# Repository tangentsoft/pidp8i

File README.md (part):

# Getting Started with the PiDP-8/I Software

## Orientation

You will be reading this either:

*   …[online][tlrm], within [the Fossil project repository][home]; or
*   …as a text file within the [source packages][src]; or
*   …in the read-only [GitHub mirror][ghm].

The latter two are secondary outputs from the first, being the PiDP-8/I
software development project’s home.

This is open source software: you are welcome to
[contribute to the project][ctrb].

[ctrb]: https://tangentsoft.com/pidp8i/doc/trunk/CONTRIBUTING.md
[ghm]:  https://github.com/tangentsoft/pidp8i
[home]: https://tangentsoft.com/pidp8i/
[src]:  https://tangentsoft.com/pidp8i/#src
[tlrm]: https://tangentsoft.com/pidp8i/doc/trunk/README.md

## Prerequisites

*   A Raspberry Pi with the 40-pin GPIO connector.

*   An SD card imaged with Raspberry Pi OS, either [stock][rpios] or
    [modified by us][bosi].

*   This software distribution, unpacked somewhere convenient within the
    filesystem on the Raspberry Pi. That’s already done on [our modified
    OS images][bosi], in `~/pidp8i`. When adding it to the stock OS, we
    recommend that you unpack it in your `HOME` directory or somewhere
    else your user has read/write access.

*   While those with no Linux and Raspberry Pi knowledge may be able to
    follow our instructions blindly, we recommend that such persons look
    at [the official Raspberry Pi documentation][rpfd], particularly
    their [Linux][rpfl] and [Raspberry Pi OS][rpfr] guides. The book
    "[Linux for Makers][lfm]" by Aaron Newcomb is also well-reviewed.

*   Building the software requires several tools and libraries, some of
    which you may not already have.

    On Raspberry Pi OS, say:

        $ sudo apt update
        $ sudo apt install build-essential libraspberrypi-dev \
             libncurses-dev perl python3-pexpect python3-yaml

    Under Homebrew, such as on macOS, say instead:

        $ brew install make perl python
        $ pip3 install --user pexpect pyyaml

    On [other compatible OSes][othos], you may need different commands.

[bosi]:  https://tangentsoft.com/pidp8i/#bosi
[lfm]:   https://www.makershed.com/products/make-linux-for-makers
[othos]: https://tangentsoft.com/pidp8i/wiki?name=OS+Compatibility
[rpfd]:  https://www.raspberrypi.org/documentation/
[rpfl]:  https://www.raspberrypi.org/documentation/linux/
[rpfr]:  https://www.raspberrypi.com/documentation/computers/os.html
[rpios]: https://www.raspberrypi.org/software/

## Enabling the SSH Server 

[That topic is covered elsewhere](./doc/OS-images.md#sshd).

## Preparing Your Pi 

If you’ve just barely unpacked Raspberry Pi OS onto an SD card and are
now trying to get the PiDP-8/I software distribution working on it, stop
and go through the [Rasbperry Pi documentation][rpd] first. At the
absolute minimum, run `raspi-config` and make sure the Localization
settings are correct. The defaults are for the United Kingdom, home of
the Raspberry Pi Foundation, so unless you live there, the defaults are
probably incorrect for *your* location.

[rpd]: https://www.raspberrypi.org/documentation/

## Getting the Software onto Your Pi 

This section is for those reading this on [our project home site][home]
or via [its GitHub mirror][ghm]. If you are instead reading this as the
`README.md` file within an unpacked distribution of the PiDP-8/I
software, [skip to the next section](#configuring).

### Transferring the Source Tarball to the Pi 

There are many ways to get the `*.tar.gz` file onto your Pi:

1.  **Copy the file to the SD card** you're using to boot the Pi.
    When inserted into a Mac or Windows PC, typically only the `/boot`
    partition mounts as a drive your OS can see.  (There's a much
    larger partition on the SD card, but most PCs cannot see it.)
    There should be enough free space left in this small partition to
    copy the tarball over.  When you boot the Pi up with that SD card,
    you will find it in `/boot`.

2.  **Pull the file down to the Pi** over the web, directly to the Pi:

        $ wget -O pidp8i.tar.gz https://goo.gl/JowPoC

    That will get you a file called `pidp8i.tar.gz` in the current
    working directory containing the latest *stable release.* To get the
    bleeding edge tip-of-trunk version instead, say:

        $ wget -O pidp8i.tar.gz https://tangentsoft.com/pidp8i/tarball

3.  **SCP the file over** to a running Pi from another machine.
    If your Pi has [OpenSSH installed and running](#sshd), you can use
    [WinSCP][wscp], [Cyberduck][cd], [FileZilla][fz] or another SCP
    or SFTP-compatible file transfer program to copy the file to the
    Pi over the network.

[cd]:   https://cyberduck.io/
[fz]:   https://filezilla-project.org/
[wscp]: https://winscp.net/eng/

4.  **Clone the Fossil repository** using the instructions in the
    [`CONTRIBUTING.md` file][ctrb]. (Best for experts or those who wish to
    become experts.)

Alternatively, switch to [the binary OS installation images][bosi],
which are a copy of Raspberry Pi OS as of our latest stable release,
with the PiDP-8/I software already downloaded, configured, and installed
for you.

### Unpacking the Software on Your Pi 

Having transferred the distribution file onto your Pi, unpack it with:

    $ tar xf pidp8i.tar.gz

## Configuring, Building and Installing 

For a stock build, say:

    $ cd ~/pidp8i
    $ ./configure && tools/mmake && sudo make install

You may want to add options to the `configure` step, described
[below](#options).

Subsequent software updates and rebuilds should not require that you
re-run the `configure` step manually, but if automatic re-configuration
fails, you can force it:

    $ make reconfig

The “`mmake`” step above will take quite a while to run, especially on
the slower Pi boards. The longest single step is building the OS/8 disk
packs from source media. Be patient; the build process almost certainly
isn’t frozen.

Only the `make install` step needs to be done via “`sudo`”. No other
step requires root privileges.

After running “`sudo make install`” the first time, you will have to log
out and back in to get the installation’s “bin” directory into your
`PATH`.

## Using the Software 

For the most part, this software distribution works like the [old stable
2015.12.15 distribution][osd]. Its [documentation][oprj] therefore
describes this software too, though there are [significant
differences][mdif].

Quick start:

1.  To start the simulator running in the background:

        $ pidp8i start

    This will happen automatically on reboot unless you disable the
    service, such as in order to run one of the various [forks of Deeper
    Thought][dt2].

2.  To attach your terminal to the running simulator, run the same
    script without an argument:

        $ pidp8i

3.  To detach from the simulator's terminal interface while leaving the
    PiDP-8/I simulator running, type <kbd>Ctrl-A d</kbd>.  You can
    re-attach to it later with a `pidp8i` command.

4.  To shut the simulator down while attached to its terminal interface,
    type <kbd>Ctrl-E</kbd> to pause the simulator, then at the `simh>`
    prompt type `quit`.  Type `help` at that prompt to get some idea of
    what else you can do with the simulator command language, or read
    the [SIMH Users' Guide][sdoc].

5.  To shut the simulator down from the command line:

        $ pidp8i stop

    That then lets you run something like [Incandescent Thought][ith]
    without conflict.

You might also find our [Learning More](/#learning) links helpful.

[ith]:     https://tangentsoft.com/pidp8i/wiki?name=Incandescent+Thought

## The Background Simulator Service 

The PiDP-8/I software distribution uses [systemd] to run the background
PDP-8 simulator as user-level service, so you needn’t give `sudo` on any
command to interact with that service, as you did in older versions of
the software.

Although you can give verbose `systemctl` commands like this:

    $ systemctl --user start pidp8i

…we’ve provided a wrapper for such commands:

    $ pidp8i start
    $ pidp8i stop
    $ pidp8i restart
    $ pidp8i status -l

*All* arguments are passed to `systemctl`, not just the first, so you
can pass any flags that `systemctl` accepts, as in the last example.

[systemd]: https://www.freedesktop.org/wiki/Software/systemd/

## Configure Script Options 

You can change many things about the way the software is built and
installed by giving options to the `configure` script:

### --prefix 

Perhaps the most widely useful `configure` script option is `--prefix`,
which lets you override the default installation directory, `/opt/pidp8i`.
There are many good reasons to change where the software gets installed,
but the default is also a good one, so unless you know for a fact that
you want to change this default, leave it alone.

For example, you might prefer that the installer put the built software
under your home directory.  This will do that:

    $ ./configure --prefix=$HOME/pidp8i && sudo make install

You might think that installing to a directory your user has complete
control over would remove the need for installing via `sudo`, but that
is not the case, since the installation script needs root privileges to
mark a few of the executables as having permission to run at high priority
levels, which improves the quality of the display, particularly with the
[incandescent lamp simulator][ils] feature enabled.

### --lowercase 

The American Standards Association (predecessor to ANSI) delivered the
second major version of the ASCII character encoding standard the same
year the first PDP-8 came out, 1965. The big new addition? Lowercase.

That bit of history means that when the PDP-8 was new, lowercase was a
fancy new feature in the computing industry. That, plus the memory
savings you get from storing [stripped ASCII][sa] as two 6-bit
characters per 12-bit PDP-8 word means that most PDP-8 software did not
expect to receive lowercase ASCII text, particularly the older software.

The PDP-8 lived long enough to see lowercase ASCII input become common
in the computing industry.

As a result, PDP-8 software reacts in many strange and wonderful
ways when you give it lowercase input. Some software copes nicely,
other software crashes, and some software just sits there dumbly
waiting for you to type something!

This configuration option lets you control how you want your simulated
PDP-8/I to react to lowercase input:

*   **auto** — The default is for the software to attempt to "do the
    right thing." The simulator is configured to send lowercase input to
    the PDP-8 software running on it. Where we have the skill, will,
    need, and time for it, we have [patched][tty] some of the software
    we distribute that otherwise would not do the right thing with
    lowercase input to make it do so.

    This is *not* the option you want if you are a purist.

*   **pass** — This passes keyboard input through to the simulator
    unchanged, and no patches are applied to the PDP-8 software we
    distribute.

    This is the option for historical purists. If you run into trouble
    getting the software to work as you expect when built in this mode,
    try enabling CAPS LOCK.

*   **upper** — This option tells the PDP-8 simulator to turn lowercase
    input into upper case. This is the behavior we used for all versions
    of the PiDP-8/I software up through v2017.04.04.  Essentially, it
    tells the software that you want it to behave as through you've got
    it connected to an uppercase-only terminal like the Teletype Model 33 ASR.

    The advantage of this mode is that you will have no problems running
    PDP-8 software that does not understand lowercase ASCII text.

    The disadvantage is obvious: you won't be able to input lowercase
    ASCII text.

    The SIMH option we enable in this mode is bidirectional, so that if
    you run a program that does emit lowercase ASCII text — such as Rick
    Murphy's version of Adventure — it will be uppercased, just like an
    ASR-33 would do.

    Another trap here is that the C programming language requires
    lowercase text, so you will get a warning if you leave the default
    option **--enable-os8-cc8** set. Pass **--disable-os8-cc8** when
    enabling **upper** mode.

[sa]:  http://homepage.cs.uiowa.edu/~jones/pdp8/faqs/#charsets
[tty]: https://tangentsoft.com/pidp8i/wiki?name=OS/8+Console+TTY+Setup

### --no-lamp-simulator 

If you build the software on a multi-core host, the PDP-8/I simulator is
normally built with the [incandescent lamp simulator][ils] feature,
which drives the LEDs in a way that mimics the incandescent lamps used
in the original PDP-8/I. (We call this the ILS for short.) This feature
takes too much CPU power to run on anything but a multi-core
Raspberry Pi, being the Pi 2 and newer full-sized boards, excluding
the Zero series.

If you configure the software on a single-core Pi — models A+, B+, and
Zero — the simulator uses the original low-CPU-usage LED driving method
instead. (a.k.a. NLS for short, named after this configuration option.)

Those on a multi-core host who want this low-CPU-usage LED driving
method can give the `--no-lamp-simulator` option to `configure`.  This
method not only uses less CPU, which may be helpful if you're trying to
run a lot of background tasks on your Pi 2 or Pi 3, it can also be
helpful when the CPU is [heavily throttled][thro].

### --serial-mod 

If you have done [Oscar's serial mod][sm1] to your PiDP-8/I PCB and the
Raspberry Pi you have connected to it, add `--serial-mod` to the
`configure` command above.

If you do not give this flag at `configure` time with these hardware
modifications in place, the front panel will not work correctly, and
trying to run the software may even crash the Pi.

If you give this flag and your PCBs are *not* modified, most of the
hardware will work correctly, but several lights and switches will not
work correctly.

### --alt-serial-mod 

This flag is for an [alternative serial mod by James L-W][sm2]. It
doesn't require mods to the Pi, and the mods to the PiDP-8/I board are
different from Oscar's.  This flag changes the GPIO code to work with
these modifications to the PiDP-8/I circuit design.

See the linked mailing list thread for details.

As with `--serial-mod`, you should only enable this flag if you have
actually done the mods as specified by James L-W.

This option is a pure alternative to [`--serial-mod`](#serial-mod): you
can leave both off, but you cannot pass both.

### --throttle <a id="throttle"</a>

See [`README-throttle.md`][thro] for the values this option takes.  If
you don't give this option, the simulator runs as fast as possible.

### --enable-savestate 

By default, the PiDP-8/I starts up with the core state undefined and
runs the boot script you’ve selected either with the IF switches or by
passing it on the command line to `pidp8i-sim` or `pdp8`.  This brings
the simulator up in a known state, with no persistence between restarts
other than what was written to the simulated storage devices before the
last shutdown.

On a real PDP-8 with core memory, however, the values in memory will
persist for weeks without power; core memory on a PDP-8 is not zeroed on
power-up, unlike RAM on a modern computer.  Since the CPU doesn’t start
executing anything on power-up in a stock PDP-8 configuration, this
means the user can toggle in a program/OS restart address with the
switch register (SR), load it into the program counter (PC) with the
Load Addr switch, then START the CPU to restart their program without
having to reload it from tape or disk.

There were also several power fail and restart options designed and made
available for the PDP-8 series throughout its lifetime. One of these —
the KP8-I for the PDP-8/I — would detect a power fail condition, then in
the brief time window while the power supply’s reservoir capacitors kept
the computer running, this option card would raise an interrupt, giving
a user-written routine up to 1 millisecond to save important registers
to core so they would persist through the power outage. Then on
power-up, it would start executing at core location 00000, where another
user routine would load those registers back from core to restart the
system where it left off before the power failed.

Giving this option gives roughtly the same effect for all generated boot
scripts: any time the simulator is shut down gracefully, it saves all
key simulator state — registers, core, device assignments, etc. — to a
disk file. Then on restart, that script will reload that saved state if
it finds the saved state file.

This is not identical to a KP8-I in that it doesn’t require any
user-written PDP-8 code to run, which is why it’s optional: it’s
ahistoric with respect to the way the included OSes normally ran.

In absence of a hardware option like the KP8-I, a more accurate
simulation would only save the core memory state to a host-side disk
file and reload it on simulator re-start. You can get that behavior atop
the current mechanism by adding commands like the following to each
bootscript you want to affect:

    EVAL HLT
    DEP L 0
    DEP AC 0
    DEP DF 0
    DEP IF 0
    DEP MQ 0
    DEP PC 0

That zeroes the key registers and prevents the CPU from running as it
normally would after giving the `RESTORE` command to SIMH.

### --disable-usb-automount 

When you install the software on a [systemd]-based Linux
system, we normally configure the OS to automatically mount USB drives
when they are initially plugged in, which allows the `SING_STEP` + `DF`
media image auto-attach feature to work smoothly. That is, if you plug
in a USB memory stick holding a `*.pt` file containing a paper tape
image, you want the simulator to be able to find it if you have the DF
switches set to 1, telling the PiDP-8/I front panel code to look for
something to attach to the simulator's paper tape reader.

This feature may interfere with other uses of USB, such as when booting
your Pi from an external USB hard disk drive. Give this option to
disable the feature.

(Alternately, you could modify our `etc/udev.rules` and/or
`bin/usb-mount` scripts so that they work cooperatively with your local
USB setup rather than conflicting with it.)

### --disable-cc8-cross 

Give this option if you do not want to build Ian Schofield's `cc8` C
cross-compiler on the host.

Because the cross-compiler is needed to build the CC8 native OS/8
compiler, disabling the cross-compiler also causes the native compiler
to be left off the bootable OS/8 RK05 disk image, as if you’d passed the
`--disable-os8-cc8` configuration option.

### --use-ock 

By default, the boot media used for the IF=0 and IF=7 cases is an
extended version of OS/8 V3D, as distributed by DEC, plus some patches
and third-party software additions, per the following sections.

For the late 2020 release, we have another more ambituous option, being
[the OS/8 Combined Kit][ock], which is the last complete release of OS/8
released by DEC. (See that link for details.)

Pass this option to boot OCK rather than OS/8 V3D.

[ock]: https://tangentsoft.com/pidp8i/dir?ci=tip&name=src/os8/ock

### --disable-os8-\* 

Several default components of the [OS/8 RK05 disk image](#os8di) used by
boot options IF=0 and IF=7 can be left out to save space and build time:

*   **--disable-os8-advent** — Leave out the [Adventure][advent] game.

*   **--disable-os8-basic-games** - Leave out the BASIC games and demos which
    primarily come from DEC's book "101 BASIC Computer Games."

*   **--disable-os8-cc8** - Leave out Ian Schofield's native OS/8 CC8
    compiler and all of its ancillary files.

*   **--disable-os8-chekmo** — Leave out John Comeau's
    [CHECKMO-II chess implementation][chess].

*   **--disable-os8-crt** — Suppress the [console rubout behavior][tty]
    enabled while building the OS/8 binary RK05 disk image. You
    probably only want to do this if you have attached a real teletype
    to your PiDP-8/I, and thus do not want video terminal style rubout
    processing.

*   **--disable-os8-dcp** — Leave out the DCP disassembler.

*   **--disable-os8-e8** — Leave out [Bill Silver’s E8][e8], an
    Emacs-like screen editor.

*   **--disable-os8-focal** - Do not install any version of FOCAL on the
    OS/8 system disk. This option sets `--disable-os8-uwfocal` and
    overrides `--enable-os8-focal69`, both discussed below.

*   **--disable-os8-fortran-ii** - Leaves out the FORTRAN II compiler,
    SABR, the linking loader (`LOADER`), the `LIBSET` tool, and the
    `*.RL` library files.  This option is ignored unless you also give
    `--disable-os8-cc8` because the OS/8 version of CC8 is built atop
    this subsystem.

*   **--disable-os8-fortran-iv** - Leave the FORTRAN IV compiler out.

*   **--disable-os8-init** - Do not install `RKB0:INIT.TX` or its “show
    on boot” script, `INIT.CM`.  Rather than disable the default on-boot
    init message, you may want to edit `media/os8/init.tx.in` to taste
    and rebuild.

*   **--disable-os8-kermit-12** - Leave out the Kermit-12 implementation
    normally installed to `RKA0:`

*   **--disable-os8-macrel** - Leave the MACREL v2 assembler and its
    associated FUTIL V8B tool out.

*   **--disable-os8-src** - Do not build the `v3d-src.rk05` disk
    image from the OS/8 source tapes.  This is not controlled by
    `--os8-minimal` because that only affects the bootable disk images.

*   **--disable-os8-uwfocal** - Leave out the U/W FOCAL V4E programming
    environment normally installed to `RKA0:`.
    
    Note that the default installation only installs `UWF16K.SV`, not
    the rest of the files on `media/os8/subsys/uwfocal*.tu56`. There is
    much more to explore here, but we cannot include it in the default
    installation set because that would overrun OS/8's limitation on the
    number of files on a volume.

You can later remove each of these after installation using
[our package manager][os8pkg].

[advent]: http://www.rickmurphy.net/advent
[chess]:  https://chessprogramming.wikispaces.com/CHEKMO-II
[e8]:     https://tangentsoft.com/e8/
[os8pat]: https://tangentsoft.com/pidp8i/doc/trunk/doc/os8-patching.md
[os8pkg]: https://tangentsoft.com/pidp8i/doc/trunk/doc/os8pkg.md

### --enable-os8-\* 

There are a few file sets not normally installed to the [OS/8 RK05 disk
image](#os8di) used by boot options IF=0 and IF=7. You can install them
with the following options:

*   **--enable-os8-music** — The `*.MU` music scores and Rich Wilson's
    associated compiler (`MUSIC.PA`) and player overlay (`PLAYOV.PA`)
    are not normally installed to the built OS/8 binary RK05 disk image
    because the Raspberry Pi reportedly does not emit eufficient RFI at
    AM radio frequencies when running these programs to cause audible
    music on a typical AM radio, the very point of these demos.  Until a
    way is found around this problem — what, low RFI is a *problem* now?
    — this option will default to "off".

*   **--enable-os8-vtedit** — This option installs a default-run macro
    pack called VTEDIT which causes the OS/8 version of TECO to run in
    full-screen mode and to react to [several special keyboard
    commands][uvte] not normally recognized by TECO.

    This feature is disabled by default because the VTEDIT macro pack
    changes the way TECO operates, and many people want TECO to behave
    like *TECO*. VTEDIT was first created during the PDP-8's commercial
    lifetime, so enabling this option is not an anachronism, but TECO is
    much older and had a much more wide-reaching impact in history, so
    we choose to provide unvarnished TECO by default.

    That having been said, people don't go to a ren fair and expect to
    experience the historical ubiquity of typhoid fever, so do not feel
    guilty if you choose to try this option.

*   **--enable-os8-focal69** — Because the default installation includes
    U/W FOCAL, we have chosen to leave [FOCAL,1969][f69] out by default
    to save space on the O/S 8 system disk. You can give this option to
    install this implementation alongside U/W FOCAL, or you can couple
    this option with `--disable-os8-uwfocal` to reverse our choice of
    which FOCAL implementation to install by default.

    You should know that the reason we made this choice is that the
    version of FOCAL,1969 we are currently shipping is fairly minimal: we
    believe we are shipping the original DEC version of FOCAL,1969 plus a
    few carefully-selected overlays. There are many more overlays and
    patches available on the Internet for FOCAL,1969, but we have not had
    time to sort through these and make choices of which ones to ship or
    how to manage which ones get installed. Thus our choice: we want to
    provide the most functional version of FOCAL by default, and within
    the limitations of the time we have chosen to spend on this, that is
    U/W FOCAL today.

    (See our [U/W FOCAL manual supplement][suppd] for a list of
    differences between these versions of FOCAL, which implicitly
    explains why we chose it.)

    It is possible that we will eventually add enough patches and
    overlays to FOCAL,1969 that it will become more powerful than U/W
    FOCAL, so we might then choose to switch the defaults, but that is
    just speculation at the time of this writing.

You can later add each of these after installation using
[our package manager][os8pkg].

[f69]:   https://tangentsoft.com/pidp8i/wiki?name=Running+FOCAL%2C1969
[suppd]: https://tangentsoft.com/pidp8i/doc/trunk/doc/uwfocal-manual-supp.md#diffs
[uvte]:  https://tangentsoft.com/pidp8i/wiki?name=Using+VTEDIT

### --os8-minimal 

This sets all `--enable-os8-*` flags to false and all `--disable-os8-*`
flags to true. This mode overrides any `--enable-os8-*` flag, so if you
want a minimal install plus just one or two features, it’s simplest to
give this flag and then use [our package manager][os8pkg] to add in the
elements you want rather than pass a bunch of `--disable-os8-*` options.

This option may not do some things you think it should:

1.  This flag's name is aspirational, not a promise of an ideal: our
    current "minimal" installation could be stripped down further. For
    example, we currently have no way to leave out OS/8's BASIC
    interpreter, even though no core OS services depend on it.

2.  This option does not affect [the `--lowercase` option](#lowercase)
    because that affects only OS/8's command interpreter and OS/8's BASIC
    implementation, so we deem it to be orthogonal to the purpose of the
    `--os8-minimal` flag, which only affects the optional post-`BUILD`
    features. You may therefore wish to give `--lowercase=none` along
    with `--os8-minimal`.

3.  This option does not affect `--disable-os8-src`, because it only
    suppresses optional features in the primary bootable OS/8 media.  If
    you want minimal OS/8 boot media without a separate source code
    data disk, give this option as well.

4.  Although this option disables *display* of the `INIT.TX` file on
    boot, the file is still generated, on purpose.  First, it acts as
    build documentation, recording what was built and when.  Second,
    you may wish to enable this welcome message later, and it’s rather
    painful to go back through the build process to generate it after
    the fact.

### --help

Run `./configure --help` for more information on your options here.

## Runtime Configuration 

The `pidp8i` command sources a Bourne shell script called `pidp8i.rc` —
normally installed in `/opt/pidp8i/etc` — which you may edit to override
certain details of the way that script runs. The intended purpose is to
give you a place to define local overrides for default variables:

### `SCREEN_MANAGER=screen` 

By default, the PiDP-8/I software distribution installs and uses [GNU
`screen(1)`][gscr] to allow the simulator to run in the background yet be
reattached from a later terminal session, then possibly later to be
backgrounded once again. Without the intermediation of something like
`screen`, the simulator would either forever be in the background — so
we’d have to export the console [another way][scons] — or we’d have to
give up on background startup, requiring that users fire the simulator
up interactively any time they wanted to use it. Using a screen manager
lets us have it both ways.

The `SCREEN_MANAGER` setting is for use by those that want to use
one of the alternatives to GNU `screen`:

*   **screen**: The default, per above.

*   [**tmux**][tmux]: A popular alternative to `screen`, especially on
    on BSD platforms. Note that the "attention" character for `tmux`
    is <kbd>Ctrl-B</kbd> by default, not <kbd>Ctrl-A</kbd> as with
    `screen`.

*   **none**: This mode is for interactive use, allowing you to
    run the installed simulator with the installed media without any
    screen manager at all.

    In this mode, the `pidp8i` and `pidp8i start` commands do the
    same thing: run the simulator directly attached to your current
    interactive terminal. The `pidp8i stop` command becomes a no-op,
    since stopping the simulator is then done in the standard SIMH way:
    <kbd>Ctrl-E, quit</kbd>.

Note that the alternative screen managers are not installed by default.
If you set `SCREEN_MANAGER=tmux`, you must then ensure that `tmux` is in
fact installed before the `pidp8i` script goes to try and use it. From
the Pi’s command line:

    $ sudo apt install tmux

Switching between configured screen managers must be done while the
simulator is stopped.

[gscr]:  https://www.gnu.org/software/screen/
[scons]: /wiki?name=Serial+or+Telnet+PDP-8+Console
[tmux]:  https://tmux.github.io/

## Simplifying Boot and Login 

The setup and installation instructions above assume you will be using
base the Raspberry Pi OS as a network server, offering SSH if nothing
else. Thus, we do not try to bypass any Linux security mechanisms, not
wanting to create an insecure island on your network.

However, if you want to run your system more as an appliance, you can
cast away some of this security to get auto-login and other convenient
behaviors:

*   [Serial or Telnet PDP-8 Console](https://tangentsoft.com/pidp8i/wiki?name=Serial+or+Telnet+PDP-8+Console)
*   [How to Run a Naked PiDP-8/i](https://tangentsoft.com/pidp8i/wiki?name=How+to+Run+a+Naked+PiDP-8/I)
*   [VNC for Remote GUI Access](https://www.raspberrypi.org/documentation/remote-access/vnc/)

## The OS/8 Disk Images 

For the first several years of the PiDP-8/I project, the OS/8 RK05 disk
image included with the PiDP-8/I software (called `os8.rk05`) was based
on an image of a real RK05 disk pack that someone allegedly found in a
salvaged PDP-8 system.  Parts of the image were corrupt, and not all of
the pieces of software worked properly with the other parts.
It was also a reflection of the time it was created and used out in the
world, which was not always what we would wish to use today.

Starting in late 2017, [several of us][aut] built a series of tools to
generate OS/8 media images from pristine source files in a repeatable,
[testable][pkgtst] way, culminating in [Bill Cattey’s `os8-run`][ori],
which backs other features like [the `--disable-os8-*` configuration
options](#disable-os8).

The resulting set of media images entirely replace the old ones and go
well beyond each besides.  All prior features are still available,
though some features present on the old images are disabled by default,
requiring either [`--enable-os8-*` configure options](#enable-os8) or
[package manager commands][os8pkg] to add features back in. Mostly,
though, the new media images are more functional than the old ones.

If you wish to know the full details of how these media images are
created, see the documentation for [`os8-run`][ori] and that for
[`class simh`][cs].

The remainder of this section describes some aspects of these media
images which are not clear from the descriptions of the `--*-os8-*`
configuration options above.

[aut]:    https://tangentsoft.com/pidp8i/doc/trunk/AUTHORS.md
[ori]:    https://tangentsoft.com/pidp8i/doc/trunk/doc/os8-run.md
[pkgtst]: https://tangentsoft.com/pidp8i/doc/trunk/doc/testing.md

### Baseline

The baseline for the bootable OS/8 media images comes from a set of
DECtapes distributed by Digital Equipment Corporation which are now
included with the PiDP-8/I software; see the [`media/os8/*.tu56`
files][os8mf]. From these files and your configuration options, the
`os8-run` script creates the baseline bootable `v3d-dist.rk05` and
`ock-dist.rk05` disk images.

The default build creates a complete OS/8 V3D system including `BUILD`
support, FORTRAN IV, MACREL v2, and more, but you can switch to an
[OCK build at compile time](#ock) if you prefer.

### Subtractions

It's pretty easy to run out of space on an OS/8 RK05 disk, not just
because of its [2 × 0.8 MWord limit][rk05td], but also because of an
OS/8 limitation in the number of files on an OS/8 filesystem. We leave
the archive of device drivers and the TD8E subsystem off the system
packs to avoid hitting this second limit. You can add them later from
[OS/8 Binary Distribution DECtape #2][bdt2], such as to create media
for a TD8E based PDP-8/e.

[rk05td]: https://en.wikipedia.org/wiki/RK05#Technical_details

### Default Additions

The OS/8 RK05 disk image build process normally installs many software
and data file sets to the disk image.  See the option descriptions
above: the ["disable" option set](#disable-os8) effectively lists those
packages that are installed by default, and the following set of
["enable" option set](#enable-os8) lists those left out by default.

### Console Enhancements

The default build enhances the console in a few ways:

1.  The SIMH PDP-8 simulator and a few select parts of OS/8 are adjusted
    to cope with lowercase input to [varying degrees](#lowercase).

2.  Rubout/backspace handling is set to assume a video terminal rather
    than a teletype by default.

You can read more about this [in the wiki][oce].

[oce]: https://tangentsoft.com/pidp8i/wiki?name=OS/8+Console+TTY+Setup

### Patches

The `v3d-dist.rk05` disk image referenced above is considered a
read-only master. A copy is made called `v3d.rk05`. This is the
default OS/8 rk05 image assigned to the IF=0 and IF=7 boot options.

In keeping with the standards of good systm management
this image incorporates all mandatory patches, as well as
optional patches appropriate to proper operation of the system.
For details on the available patches, the selection criteria,
and information about other optional patches see the [OS/8 system patches][os8pat]
document.

[bdt2]:  https://tangentsoft.com/pidp8i/file/media/os8/al-4712c-ba-os8-v3d-2.1978.tu56
[cl]:    https://tangentsoft.com/pidp8i/doc/trunk/ChangeLog.md
[cs]:    https://tangentsoft.com/pidp8i/doc/trunk/doc/class-simh.md
[os8mf]: https://tangentsoft.com/pidp8i/file/media/os8
[tlrm]:  https://tangentsoft.com/pidp8i/doc/trunk/README.md

## The OS/8 TU56 Tape Image 

As with the [OS/8 disk image](#os8di), this distribution’s build system
can create custom TU56 tape images from pristine source media.  This
replaces the old `os8.tu56` binary image previously distributed with
this software.

The build system actually creates four such tape images according to a
2×2 matrix of choices:

*   **--boot-tape-version** — The default value is “`v3f`”, meaning
    that the boot tape is based on OS/8 V3F. Give “`v3d`” to boot from
    a OS/8 V3D tape instead. See the wiki article [OS/8 V3D vs
    V3F][os8ver] for the implications of this choice.

*    **--boot-tape-config** — The default value is “`tc08`”. Give
    “`td12k`” to use a tape image configured with the TD12K DECtape
    controller driver built in. See the wiki article [TC08 vs
    TD12K][os8td] for the reason you’re given a choice here.

[os8td]:  https://tangentsoft.com/pidp8i/wiki?name=TD8E+vs+TC08
[os8ver]: https://tangentsoft.com/pidp8i/wiki?name=OS/8+V3D+vs+V3F

## Overwriting the Local Simulator Setup 

When you run `sudo make install` step on a system that already has an
existing installation, it purposely does not overwrite two classes of
files:

1.  **The binary PDP-8 media files**, such as the RK05 disk image that
    holds the OS/8 image the simulator boots from by default. These media
    image files are considered "precious" because you may have modified
    the OS configuration or saved personal files to the disk the OS
    boots from, which in turn modifies this media image file out in the
    host operating environment.

2.  **The PDP-8 simulator configuration files**, installed as
    `$prefix/share/boot/*.script`, which may similarly have local
    changes, and thus be precious to you.

Sometimes this "protect the precious" behavior isn't what you want.
(Gollum!) One common reason this may be the case is that you've damaged
your local configuration and want to start over. Another common case is
that the newer software you're installing contains changes that you want
to reflect into your local configuration.

You have several options here:

1.  If you just want to reflect the prior PDP-8 simulator configuration
    file changes into your local versions, you can hand-edit the
    installed simulator configuration scripts to match the changes in
    the newly-generated `boot/*.script` files under the build directory.

2.  If the change is to the binary PDP-8 media image files — including
    the [generated OS/8 disk images](#os8di) — and you're unwilling to
    overwrite your existing ones wholesale, you'll have to mount both
    versions of the media image files under the PDP-8 simulator and copy
    the changes over by hand.

3.  If your previously installed binary OS media images — e.g. the
    [OS/8 RK05 disk image](#os8di) that the simulator boots from by
    default — are precious but the simulator configuration scripts
    aren't precious, you can just copy the generated `boot/*.script`
    files from the build directory into the installation directory,
    `$prefix/share/boot`.  (See the `--prefix` option above for the
    meaning of `$prefix`.)

4.  If neither your previously installed simulator configuration files
    nor the binary media images are precious, you can force the
    installation script to overwrite them both with a
    `sudo make mediainstall` command after `sudo make install`.

    Beware that this is potentially destructive! If you've made changes
    to your PDP-8 operating systems or have saved files to your OS
    system disks, this option will overwrite those changes!

## Testing Your PiDP-8/I Hardware 

You can test your PiDP-8/I LED and switch functions with these commands:

    $ pidp8i stop
    $ pidp8i-test

You may have to log out and back in before the second command will work,
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
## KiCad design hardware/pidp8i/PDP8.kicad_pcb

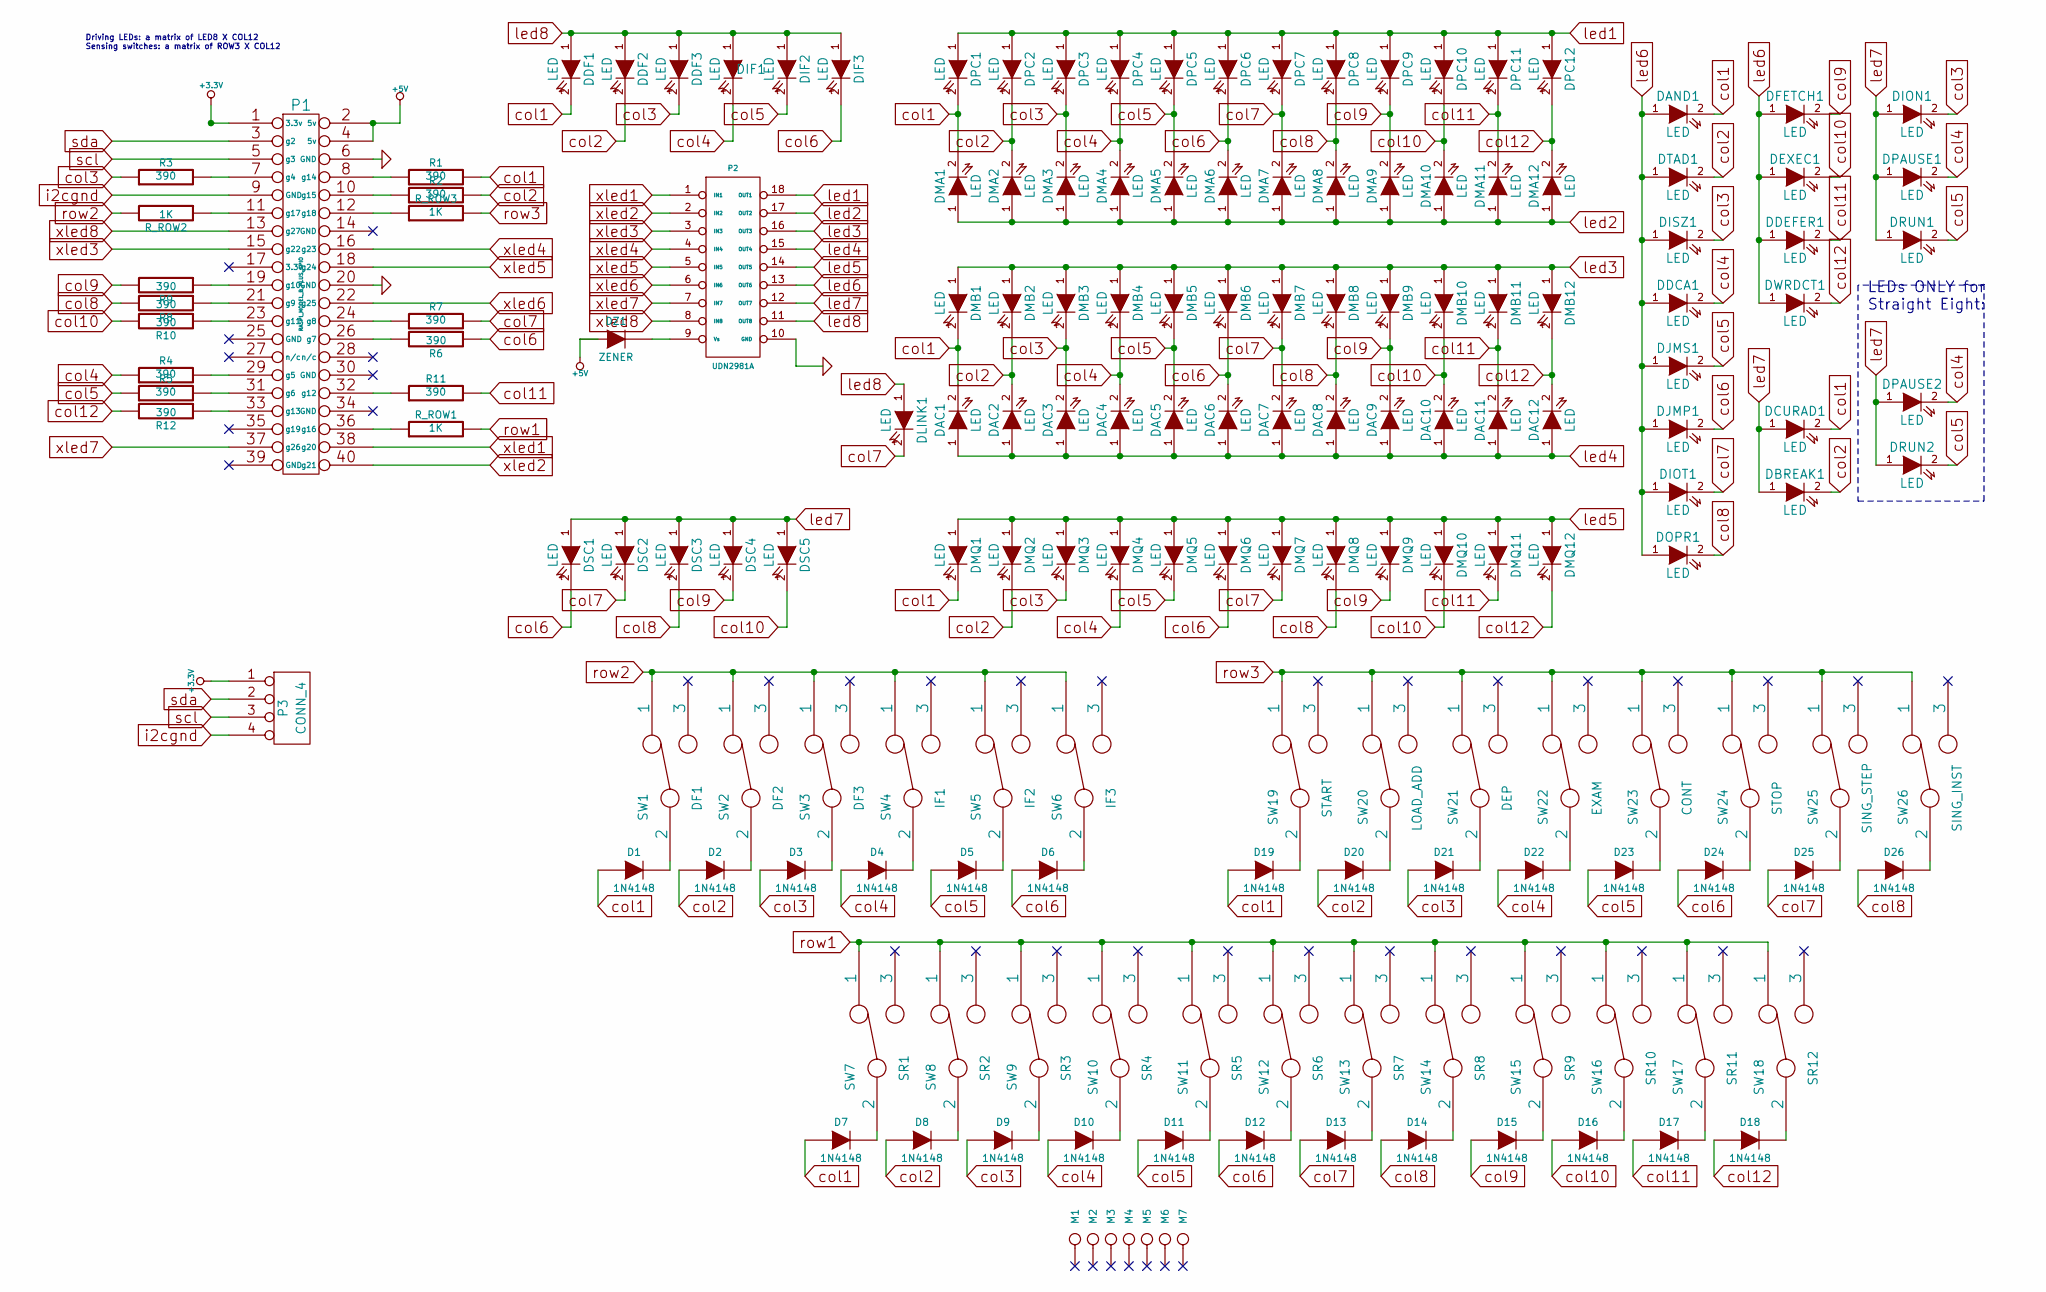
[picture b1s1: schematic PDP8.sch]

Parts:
D1, D2, D3, D4, D5, D6, D7, D8, D9, D10, D11, D12, D13, D14, D15, D16, D17, D18, D19, D20, D21, D22, D23, D24, D25, D26: 1N4148
DAC1, DAC2, DAC3, DAC4, DAC5, DAC6, DAC7, DAC8, DAC9, DAC10, DAC11, DAC12: LED
DAND1: LED
DBREAK1: LED
DCURAD1: LED
DDCA1: LED
DDEFER1: LED
DDF1, DDF2, DDF3: LED
DEXEC1: LED
DFETCH1: LED
DIF1, DIF2, DIF3: LED
DION1: LED
DIOT1: LED
DISZ1: LED
DJMP1: LED
DJMS1: LED
DLINK1: LED
DMA1, DMA2, DMA3, DMA4, DMA5, DMA6, DMA7, DMA8, DMA9, DMA10, DMA11, DMA12: LED
DMB1, DMB2, DMB3, DMB4, DMB5, DMB6, DMB7, DMB8, DMB9, DMB10, DMB11, DMB12: LED
DMQ1, DMQ2, DMQ3, DMQ4, DMQ5, DMQ6, DMQ7, DMQ8, DMQ9, DMQ10, DMQ11, DMQ12: LED
DOPR1: LED
DPAUSE1, DPAUSE2: LED
DPC1, DPC2, DPC3, DPC4, DPC5, DPC6, DPC7, DPC8, DPC9, DPC10, DPC11, DPC12: LED
DRUN1, DRUN2: LED
DSC1, DSC2, DSC3, DSC4, DSC5: LED
DTAD1: LED
DWRDCT1: LED
DZ1: ZENER
M1, M2, M3, M4, M5, M6, M7: M
P1: RASPI_MODEL_B_PLUS_GPIO
P2: UDN2981A
P3: CONN_4
R1, R2, R3, R4, R5, R6, R7, R8, R9, R10, R11, R12: 390
R_ROW1, R_ROW2, R_ROW3: 1K
SW1: DF1
SW2: DF2
SW3: DF3
SW4: IF1
SW5: IF2
SW6: IF3
SW7: SR1
SW8: SR2
SW9: SR3
SW10: SR4
SW11: SR5
SW12: SR6
SW13: SR7
SW14: SR8
SW15: SR9
SW16: SR10
SW17: SR11
SW18: SR12
SW19: START
SW20: LOAD_ADD
SW21: DEP
SW22: EXAM
SW23: CONT
SW24: STOP
SW25: SING_STEP
SW26: SING_INST

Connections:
+3.3V: P1.1 (3.3v), P3.1; also elsewhere on the board
+5V: DZ1.1 (A), P1.2 (5v), P1.4 (5v)
GND: P1.6 (GND), P1.20 (GND), P2.10 (GND)
unnamed: DZ1.2 (K), P2.9 (Vs)
unnamed: D1.2 (K), SW1.2
unnamed: D6.2 (K), SW6.2
unnamed: D5.2 (K), SW5.2
unnamed: D4.2 (K), SW4.2
unnamed: D3.2 (K), SW3.2
unnamed: D2.2 (K), SW2.2
unnamed: P1.7 (g4), R3.2
unnamed: P1.11 (g17), R_ROW2.1
unnamed: P1.19 (g10), R9.1
unnamed: P1.21 (g9), R8.1
unnamed: P1.29 (g5), R4.2
unnamed: P1.31 (g6), R5.2
unnamed: P1.33 (g13), R12.1
unnamed: P1.12 (g18), R_ROW3.1
unnamed: P1.24 (g8), R7.1
unnamed: P1.32 (g12), R11.1
unnamed: P1.36 (g16), R_ROW1.1
unnamed: D23.2 (K), SW23.2
unnamed: D22.2 (K), SW22.2
unnamed: D21.2 (K), SW21.2
unnamed: D20.2 (K), SW20.2
unnamed: D19.2 (K), SW19.2
unnamed: P1.8 (g14), R1.1
unnamed: P1.10 (g15), R2.1
unnamed: P1.23 (g11), R10.1
unnamed: P1.26 (g7), R6.2
unnamed: D24.2 (K), SW24.2
unnamed: D12.2 (K), SW12.2
unnamed: D18.2 (K), SW18.2
unnamed: D17.2 (K), SW17.2
unnamed: D16.2 (K), SW16.2
unnamed: D15.2 (K), SW15.2
unnamed: D14.2 (K), SW14.2
unnamed: D13.2 (K), SW13.2
unnamed: D11.2 (K), SW11.2
unnamed: D10.2 (K), SW10.2
unnamed: D9.2 (K), SW9.2
unnamed: D8.2 (K), SW8.2
unnamed: D7.2 (K), SW7.2
unnamed: D26.2 (K), SW26.2
unnamed: D25.2 (K), SW25.2
col1: D1.1 (A), D7.1 (A), D19.1 (A), DAC1.2 (K), DAND1.2 (K), DCURAD1.2 (K), DDF1.2 (K), DMA1.2 (K), DMB1.2 (K), DMQ1.2 (K), DPC1.2 (K), R1.2
col2: D2.1 (A), D8.1 (A), D20.1 (A), DAC2.2 (K), DBREAK1.2 (K), DDF2.2 (K), DMA2.2 (K), DMB2.2 (K), DMQ2.2 (K), DPC2.2 (K), DTAD1.2 (K), R2.2
col3: D3.1 (A), D9.1 (A), D21.1 (A), DAC3.2 (K), DDF3.2 (K), DION1.2 (K), DISZ1.2 (K), DMA3.2 (K), DMB3.2 (K), DMQ3.2 (K), DPC3.2 (K), R3.1
col4: D4.1 (A), D10.1 (A), D22.1 (A), DAC4.2 (K), DDCA1.2 (K), DIF1.2 (K), DMA4.2 (K), DMB4.2 (K), DMQ4.2 (K), DPAUSE1.2 (K), DPAUSE2.2 (K), DPC4.2 (K), R4.1
col5: D5.1 (A), D11.1 (A), D23.1 (A), DAC5.2 (K), DIF2.2 (K), DJMS1.2 (K), DMA5.2 (K), DMB5.2 (K), DMQ5.2 (K), DPC5.2 (K), DRUN1.2 (K), DRUN2.2 (K), R5.1
col6: D6.1 (A), D12.1 (A), D24.1 (A), DAC6.2 (K), DIF3.2 (K), DJMP1.2 (K), DMA6.2 (K), DMB6.2 (K), DMQ6.2 (K), DPC6.2 (K), DSC1.2 (K), R6.1
col7: D13.1 (A), D25.1 (A), DAC7.2 (K), DIOT1.2 (K), DLINK1.2 (K), DMA7.2 (K), DMB7.2 (K), DMQ7.2 (K), DPC7.2 (K), DSC2.2 (K), R7.2
col8: D14.1 (A), D26.1 (A), DAC8.2 (K), DMA8.2 (K), DMB8.2 (K), DMQ8.2 (K), DOPR1.2 (K), DPC8.2 (K), DSC3.2 (K), R8.2
col9: D15.1 (A), DAC9.2 (K), DFETCH1.2 (K), DMA9.2 (K), DMB9.2 (K), DMQ9.2 (K), DPC9.2 (K), DSC4.2 (K), R9.2
col10: D16.1 (A), DAC10.2 (K), DEXEC1.2 (K), DMA10.2 (K), DMB10.2 (K), DMQ10.2 (K), DPC10.2 (K), DSC5.2 (K), R10.2
col11: D17.1 (A), DAC11.2 (K), DDEFER1.2 (K), DMA11.2 (K), DMB11.2 (K), DMQ11.2 (K), DPC11.2 (K), R11.2
col12: D18.1 (A), DAC12.2 (K), DMA12.2 (K), DMB12.2 (K), DMQ12.2 (K), DPC12.2 (K), DWRDCT1.2 (K), R12.2
i2cgnd: P1.9 (GND), P3.4; also elsewhere on the board
led1: DPC1.1 (A), DPC2.1 (A), DPC3.1 (A), DPC4.1 (A), DPC5.1 (A), DPC6.1 (A), DPC7.1 (A), DPC8.1 (A), DPC9.1 (A), DPC10.1 (A), DPC11.1 (A), DPC12.1 (A), P2.18 (OUT1)
led2: DMA1.1 (A), DMA2.1 (A), DMA3.1 (A), DMA4.1 (A), DMA5.1 (A), DMA6.1 (A), DMA7.1 (A), DMA8.1 (A), DMA9.1 (A), DMA10.1 (A), DMA11.1 (A), DMA12.1 (A), P2.17 (OUT2)
led3: DMB1.1 (A), DMB2.1 (A), DMB3.1 (A), DMB4.1 (A), DMB5.1 (A), DMB6.1 (A), DMB7.1 (A), DMB8.1 (A), DMB9.1 (A), DMB10.1 (A), DMB11.1 (A), DMB12.1 (A), P2.16 (OUT3)
led4: DAC1.1 (A), DAC2.1 (A), DAC3.1 (A), DAC4.1 (A), DAC5.1 (A), DAC6.1 (A), DAC7.1 (A), DAC8.1 (A), DAC9.1 (A), DAC10.1 (A), DAC11.1 (A), DAC12.1 (A), P2.15 (OUT4)
led5: DMQ1.1 (A), DMQ2.1 (A), DMQ3.1 (A), DMQ4.1 (A), DMQ5.1 (A), DMQ6.1 (A), DMQ7.1 (A), DMQ8.1 (A), DMQ9.1 (A), DMQ10.1 (A), DMQ11.1 (A), DMQ12.1 (A), P2.14 (OUT5)
led6: DAND1.1 (A), DDCA1.1 (A), DDEFER1.1 (A), DEXEC1.1 (A), DFETCH1.1 (A), DIOT1.1 (A), DISZ1.1 (A), DJMP1.1 (A), DJMS1.1 (A), DOPR1.1 (A), DTAD1.1 (A), DWRDCT1.1 (A), P2.13 (OUT6)
led7: DBREAK1.1 (A), DCURAD1.1 (A), DION1.1 (A), DPAUSE1.1 (A), DPAUSE2.1 (A), DRUN1.1 (A), DRUN2.1 (A), DSC1.1 (A), DSC2.1 (A), DSC3.1 (A), DSC4.1 (A), DSC5.1 (A), P2.12 (OUT7)
led8: DDF1.1 (A), DDF2.1 (A), DDF3.1 (A), DIF1.1 (A), DIF2.1 (A), DIF3.1 (A), DLINK1.1 (A), P2.11 (OUT8)
row1: R_ROW1.2, SW7.1, SW8.1, SW9.1, SW10.1, SW11.1, SW12.1, SW13.1, SW14.1, SW15.1, SW16.1, SW17.1, SW18.1
row2: R_ROW2.2, SW1.1, SW2.1, SW3.1, SW4.1, SW5.1, SW6.1
row3: R_ROW3.2, SW19.1, SW20.1, SW21.1, SW22.1, SW23.1, SW24.1, SW25.1, SW26.1
scl: P1.5 (g3), P3.3; also elsewhere on the board
sda: P1.3 (g2), P3.2; also elsewhere on the board
xled1: P1.38 (g20), P2.1 (IN1)
xled2: P1.40 (g21), P2.2 (IN2)
xled3: P1.15 (g22), P2.3 (IN3)
xled4: P1.16 (g23), P2.4 (IN4)
xled5: P1.18 (g24), P2.5 (IN5)
xled6: P1.22 (g25), P2.6 (IN6)
xled7: P1.37 (g26), P2.7 (IN7)
xled8: P1.13 (g27), P2.8 (IN8)

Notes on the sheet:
Driving LEDs: a matrix of LED8 X COL12 Sensing switches: a matrix of ROW3 X COL12
LEDs ONLY for Straight Eight:

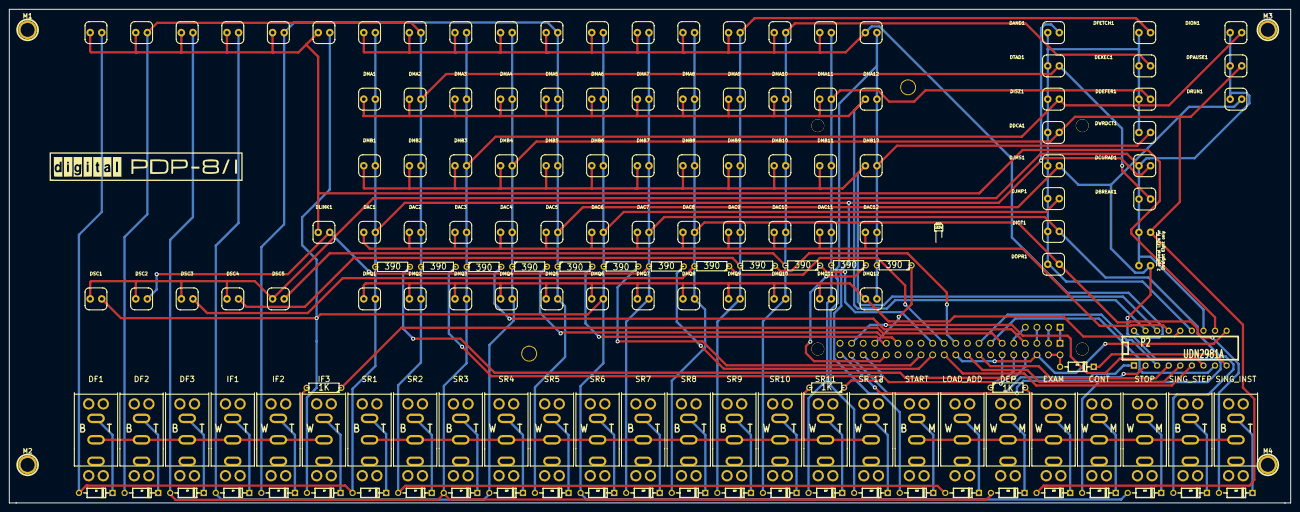
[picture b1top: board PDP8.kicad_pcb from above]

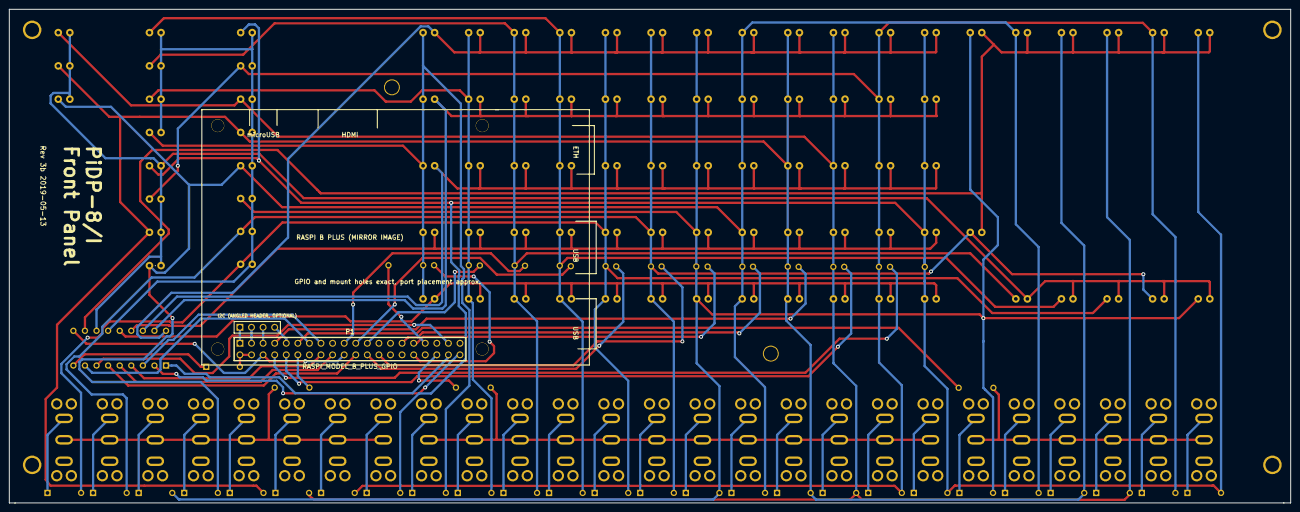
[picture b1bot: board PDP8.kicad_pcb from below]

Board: 2 copper layers, 281.0 x 108.2 mm, 168 parts (2 on the bottom side), 79 nets.

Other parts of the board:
1PIN: P***; 1pin
I2C (ANGLED HEADER, OPTIONAL): CONN_4; PIN_ARRAY_4x1

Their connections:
+3.3V: I2C (ANGLED HEADER, OPTIONAL).1; also elsewhere on the board
i2cgnd: I2C (ANGLED HEADER, OPTIONAL).4; also elsewhere on the board
scl: I2C (ANGLED HEADER, OPTIONAL).3; also elsewhere on the board
sda: I2C (ANGLED HEADER, OPTIONAL).2; also elsewhere on the board

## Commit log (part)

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2020-05-08 The BASIC and FORTRAN II rk05 object image is now built. The Core Control Block values match what is in SYS: TODO: Put these onto a system disk and test them.
    FossilOrigin-Name: 476cfa0ca6286bbc39058bbd6ac480373eedacdc
2020-05-09 Fixed all "@include @srcdir@/boot/common.script" from boot/*.script.in: common.script is generated from common.script.in, so it lands in @builddir@, not in @srcdir@. This distinction only matters whe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
    FossilOrigin-Name: a8f891a345b99969218792cf9272107ca6dcf694522f9e4d507c84eb85b7a208
2020-05-10 An update of the cc8 manual to include the current functionality of the native compiler.
    FossilOrigin-Name: d38ea4e835bcb5ae39eb70e119d8a5fad106d8c9
2020-05-11 Change to c8.c to correctly manage ' character.
    FossilOrigin-Name: 05b89395b231069839af729348be38960483747f
2020-05-16 A fast tool to unpack images from Vince Slyngstad.
    FossilOrigin-Name: 9cf8e0d48ab307a93f091c6f6fe0787fbef7e98e
2020-05-18 I keep forgetting to ADD stuff. NOW we have os8-cmp.in. :-(
    FossilOrigin-Name: d2f68d78fa983f70bba1796f7fc563884b7643fb
2020-05-26 CC8 comment fix
    FossilOrigin-Name: 65085ceb9a236e80d2d15f512effdc04622e70cda7b0e0eda5be14ea6698fbad
2020-06-11 Improved error reporting from os8_command: I was relying too much on the "print caller string" functionality, when instead I should have been acting on error status and printing good messages. I miss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
    FossilOrigin-Name: 83d6d9ac2da1bc153c3c78e7737e53845e77bd05
2020-06-13 Merged as much of E8's Makefile stuff into our Makefile.in as makes sense. Basically, only the creation of e8-manual.pdf and the upload to the repo as UV content.
    FossilOrigin-Name: bca79f692bf2997df5e455ac6d45f63bbef82338bbb3c05a6fe9867d9f262979
2020-06-15 URL fix
    FossilOrigin-Name: 47bc55b175242fbdabf771ed0f7d0893e48d11800b637d126eec9c26eeca9cc1
2020-06-15 This is a significant re-write of the native compiler. Numerous additions have been implemented. Missing features from K&R are now only struct/float/function pointers.
    FossilOrigin-Name: cf7e75b64fa03df999c09f8781f2e01e0562aa89
2020-06-16 Update n8.c to allow for long input lines.
    FossilOrigin-Name: ce122dc32134469d203ef8a33009a585754ae2f5
2020-06-17 Saw a typo. Fixed it.
    FossilOrigin-Name: 572119ed707ff9bb41ba79b36cc76df19ac28bd7
2020-06-21 Renamed uni and all its manifestations to ock.
    FossilOrigin-Name: 37f2c27165269907794c2ab76f585896c5e19551
2020-07-10 Yet another critical script I failed to ADD. Maybe this fully fixes bug 8d1502e9eed
    FossilOrigin-Name: 1f1ac14196a8cf81618ce422f204b90c5d747bdc
2020-07-31 Implemented the clearer demarkation of different levels of OS8 boot media, as per Forum discussion: https://tangentsoft.com/pidp8i/forumpost/dcf09a8902
    FossilOrigin-Name: c548a7866c19ce69e168e9be44109bd8005b98ba
2020-08-15 Long overdue fixup of pexpect error reporting: pexpect used to hang for 30 seconds, timeout, and give a messy traceback when it got confused. This was NOT helpful because the traceback didn't give th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
    FossilOrigin-Name: ff1e4919aa755f5e3e9b7a154c8ac3c8ba88e369
2020-09-11 Turn in-line sub-command parser setup to table driven for loop.
    FossilOrigin-Name: 7e3f1767f4ddd9f14b1bcb2eae66c928c2f66a51
2020-09-13 Code cleanups in the new os8pkg loop within auto.def: remove redundant "then", remove pointless "set result", popped "exec" calls out of bracket expression now that we aren't pointlessly saving the r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
    FossilOrigin-Name: d468b646bead72ceadec292393a23026240965a9e94dae59e3ed252c9c5a872a
2020-09-17 Typo fix
    FossilOrigin-Name: d31d2dcd869becde3973ac6f3757709825b38ea2822a2967be9d14536e60e549
2020-10-27 Implemented and documented install and uninstall commands. Updated advent.pspec to contain cleanups for uninstall.
    FossilOrigin-Name: e1d2257810d5c142c435ab6ec35cb8bbff9d8198
2020-10-28 Remove debugging bit from basic-games.pspec.
    FossilOrigin-Name: 7a9b5fe2131bcdc5020a2344971607ad4b824745
2020-10-29 Assorted improvements to the HACKERS.md file, including the addition of a workflow Pikchr showing the life cycle of a ticket.
    FossilOrigin-Name: 8c59adde5704a2f5c18d75dfdd08d20d8605d760846d2ee22a7ef0715dd26d6e
2020-10-29 Updated the release process doc
    FossilOrigin-Name: 36cfa1dcebc05f6dafd1e70200a45b10f95389342c7b77ae73ebf493dd10f807
2020-10-31 Convert binary blob CHESS.SV copied in from media/os8/local.tu56 under the control of config option "chess" to a build from source CHEKMO.SV and CHEKMO.TX controlled by config option "chekmo". Fix a 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
    FossilOrigin-Name: 2573adc1ca59137efc0e045d39d78babe28ddda4
2020-10-31 Fixed a problem in previous that prevents most of the commands from running.
    FossilOrigin-Name: 4f048240b4f627bd6be2b7eed40f04f2d2d21b4bf5804712167ffb8805f25efb
2020-10-31 Added a clean-glob setting, listing the files we know can be unconditionally deleted on "fossil clean" without saving them to the undo buffer. Also tweaked the ignore-glob setting to cooperate.
    FossilOrigin-Name: b7b60dae32b51c3e2fa1bac4f0cf98e38c64ce4bca63a3c843546e114bf158f6
2020-11-01 Credit upstream for focal69. Rename source files to accurately follow upstream.
    FossilOrigin-Name: 2fe0f9d65f54d300e630cb1fd4eab4cc22b92d34
2020-11-01 Move the patched FORLIB.RL binary out of media/os8/local.tu56 to the source tree. TODO: Pull in all the sources and create a forlib-51.10M-tu56.os8 script that builds it from source.
    FossilOrigin-Name: 4d4aa628a0a0fc4d724aa12b9d07e87b049897f1
2020-11-03 Backported the merger of the PiDP-8/I and MySQL++ "Submitting Patches" and GitHub mirroring sections of CONTRIBUTING.md to minimize differences.
    FossilOrigin-Name: 396bbd521353b995b80831375f8d85804adf91acde5a5b1cf5884459b40eed18
2020-11-04 Replaced embedded doc references to HACKERS.md with CONTRIBUTING.md, so clicks don't have to go through the HTTP redirect.
    FossilOrigin-Name: 64c9b68d745da5509c62dc89985ece2c90c3ed604d436b1670d570a107939bbe
2020-11-10 API change: Allow us to run a script on an in-memory file created with Python io library.
    FossilOrigin-Name: 5eba589cdebe3a5d25a220e7c43945ebe540ed6a
2020-11-12 Converted the inventory to an HTML table without all the cross-page links to other content. I copied this version into the Wiki. TODO: Pick ONE of these either the Wiki or the README.md as canon.
    FossilOrigin-Name: dea21330770f74c368a31bddf93d3a56802447fa
2020-11-14 Needed to remove the temp file created for the boot device.
    FossilOrigin-Name: a090dfb35b9fb01ba06b07df3cf4728026a17a4c
2020-11-15 Added ability to process multiple tests on command. Removed superfluous "program" item in test files. Added test of fib to cc8.
    FossilOrigin-Name: 7d40ec51edad387e7a87a45c74799dd532171fc3
2020-11-17 Edit pass on the os8-progtest doc.
    FossilOrigin-Name: 752895916720e85659cd00849f4dc8ada8120a63d8e892caadae05e8e7bfb67e
2020-11-20 Another snapshot of class-os8script.md Still brainstorming content.
    FossilOrigin-Name: bcefc61e95c4ea98d3e1a215de3a43b4a004052d
2020-12-05 Add documentation of the --exitfirst option and the work-around for long output.
    FossilOrigin-Name: 0c003f5ef9975df5947247f9039772b8f7788732
2020-12-07 Snapshot. Almost, but not quite done. TODO: 1. Finish the narrative on how to write a complete program. 2. Confirm all the links work. 3. Completeness, style, and grammar check.
    FossilOrigin-Name: 0a1d0ed404239329ad40f7481fc9fdc77122d1c4
2020-12-16 Tightened up the top-level README.md file some more.
    FossilOrigin-Name: 4befb5ef3cada52836d5db3d0e1ed10802836b979b4f363a73658aec13cf001d
2021-02-04 Fixed a Markdown rendering problem. (Unwanted line break in literal text.)
    FossilOrigin-Name: b91714a2ed4f34aa6e24a6ce1cc107163d4e346c8011b08cbe6f203d94498a0c
2021-02-08 Updated ChangeLog for the imminent release
    FossilOrigin-Name: 600a9459a8fb7a331592d8ea1c3a9178f15758f7c211d1810902ac7c784a0ef2
2021-02-08 Lowercased all the file names in pspec/advent.pspec to match their new case in the repo. Without this, the build only succeeds on systems with case-insensitive filesystems like macOS, and then only w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
    FossilOrigin-Name: c425495e2c4ebbd13de6903b613dbb540cbe0b44359d38c300bf6df4452b59e9
2021-02-08 Removed the last remaining symlinks, being those for CC8's init.h and libc.h files, which CC8 always looks for in the CWD, yet which need to exist in 3 different places. Creating symlinks for the oth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
    FossilOrigin-Name: 3fcbc85340931bdc7e149bb274fa11b656629a22ca240827dcf3d3e18f77e1db
2021-02-08 tools/autosetup-update now removes the contents of autosetup/* before doing its work so we track upstream deletions properly. This results in a lot of files being deleted, but it looks like it's a re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
    FossilOrigin-Name: 2dbb85383bb1c8cd5d7af8f97fb7c17fac15eeff1d29741cbed009bf5e1b14ac
2021-02-15 Upped minimum SD card requirement from 2GB to 8GB after "bosi init" failed with an out-of-space message on the "apt upgrade" step, even after removing the biggest disk hogs we can most do without. Th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
    FossilOrigin-Name: 0136f1193fb9e6a8b1658b320ed3f8ffc6e33f63f9e204c0927355906d527095
2021-02-15 Swapped commands in "sudo time" constructs in bosi so we use the calling shell's builtin version instead of /usr/bin/time, since at least on macOS, the builtin's output is clearer. Tweaked the prior 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
    FossilOrigin-Name: 1ef732c32cbb6109236a134717f142cf02f8c481a0c2b2ee3b8426670d8fd9f7
2021-02-15 Reworked the logic in the new "bosi build nls" code so it copies any missing images from UV, rather than blindly copy all of them only when the first one is missing. This lets you re-run the script l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
    FossilOrigin-Name: 5ec88693acbba67179220c0064101644d2b092d90fa7c72ef454b2adc8420354
2021-04-23 Updated to the latest SIMH to fix a problem with TSS/8 booting. It seems they updated some of the device handling since the Feb 3 update we did just prior to the current stable release.
    FossilOrigin-Name: f02ebe72df1353559c748ef3ea2691e2b261939c3883979c0ae3d6c6f7149a75
2021-10-18 Removed the "PiDP add" and "PiDP end" comments. Those markers are only for injections into upstream files; this one's new.
    FossilOrigin-Name: 151d16011d9e0ce44010dff59b7f8c3f246672e8
2021-11-08 Begin branch to fix some issues related to the LED panel display
    FossilOrigin-Name: 556e1a695255326691cfb019eb432df85ca38f52
2021-12-04 First apparently working version of the cycle-realistic PiDP-8/I. This makes the Sing Step switch on the PiDP-8/I front panel behave the same as on a real -8 (subject to a minor risk that MA and MB m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
    FossilOrigin-Name: 241d799d532dcfe044cce2e341b7f0bc5016486f
2022-01-08 Updated SIMH to get Rick Murphy's FPP bug fix.
    FossilOrigin-Name: b74012df757f7cead987373156e74c5cf862ce09936b47010d6ade48d6811ed6
2023-03-06 Add more debug output to os8-progtest Refine basic-games.yml because a race condition broke it on M2 Macs. I think this refinement will be definitive. Fingers crossed.
    FossilOrigin-Name: c124f7a6e7179e9aaed81be211636fc43884e3d1
2024-05-10 First attempt to integrate new gpio handler from Oscar Vermeulen. Won't build on the Mac because pinctrl.c uses non-portable reallocarray. Gotta fix that.
    FossilOrigin-Name: b468cd1c6f0b67e05d8859f506d4e7771f0ed4df
2024-05-13 Fixes to get things building again on my pi. Pruned a couple superfluous lines I'd previously made in auto.def. TODO: See if I can get pidp8i-test blinking lights again.
    FossilOrigin-Name: 6fb29f08a25d8d0adb331af27d7deb3617e3291a
2024-05-19 We weren't initializing the GPIO pin direction in the nls interface like we did in with ils. This fixes pidp8i-test and scanswitch.
    FossilOrigin-Name: 1eaccc22602b5af12158a8ec5ddb0d849c510bb2
2024-06-03 After splitting out the PI_BINS I broke install. This should fix it.
    FossilOrigin-Name: 4b84468f431c0ec95a33b7ad0390e33b28b61ab4
2024-06-14 revert pinctrl chaching optim., not worth it. Moved ILS/NLS switching logic from compile time to runtime / configuration file
    FossilOrigin-Name: ccedb853c90ac901b26c70cc2e89838bb56a4990
2024-06-30 Enable ILS mode in single-step/single-instruction mode. Enable ILS in more of the throttling modes, including throttling to very slow speeds like 1 instruction per second
    FossilOrigin-Name: 3b3fcb8834282317b3fb0447d02aa0e067ef8fa5
2024-12-19 Made several strings in bin/os8pkg.in "raw" to get around [https://stackoverflow.com/q/52335970 | a recent SyntaxWarning gripe].
    FossilOrigin-Name: d29fd7be58b97024184c0806869d6250a4b451fb8f8de5f61c97a1dc125a11e6

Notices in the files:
README.md:
License:
Copyright © 2016-2020 by Warren Young. This document is licensed under
the terms of [the SIMH license][sl].
